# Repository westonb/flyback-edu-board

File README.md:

# flyback-edu-board
A basic flyback converter optimized for teaching educational labs. 
Designed for Stanford's EE 254 and optimized for the JLC assembly service. 

The board is based on the [UC3482B](https://www.onsemi.com/pdf/datasheet/uc3842b-d.pdf) current mode controller IC and provides a regulated 5V output than can be used to charge a phone. 

The board is designed to aid in teaching fundamentals of power electronics, lab techniques, and control theory. 
It is designed with test points on most relevant circuit nodes. 
The primary and secondary current can be measured with the shunt resistors on the PCB, so most work on the board can be done without the use of a current probe. 

In line with the educational goals the board is designed for low cost assembly. The kicad schematic includes LCSC part numbers for assembly at JLC. At 2023 prices a 25 unit build is <$15 with the JLC PCBA service. 

PCB designed in KICAD 6.

## Specifications
|   |   |
| -------- | -------- |
| Input Voltage | 12V - 36V |
| Output Voltage| 5V |
| Output Current | 1.5A |

## Features
- Built in DC and stepped resistive load
- USB A output
- Short and reverse polarity protection
- Output protected from over-voltage due to regulation fault
- Test points on critical circuit nodes
- Switchable between direct and opto-isolated voltage regulation loops

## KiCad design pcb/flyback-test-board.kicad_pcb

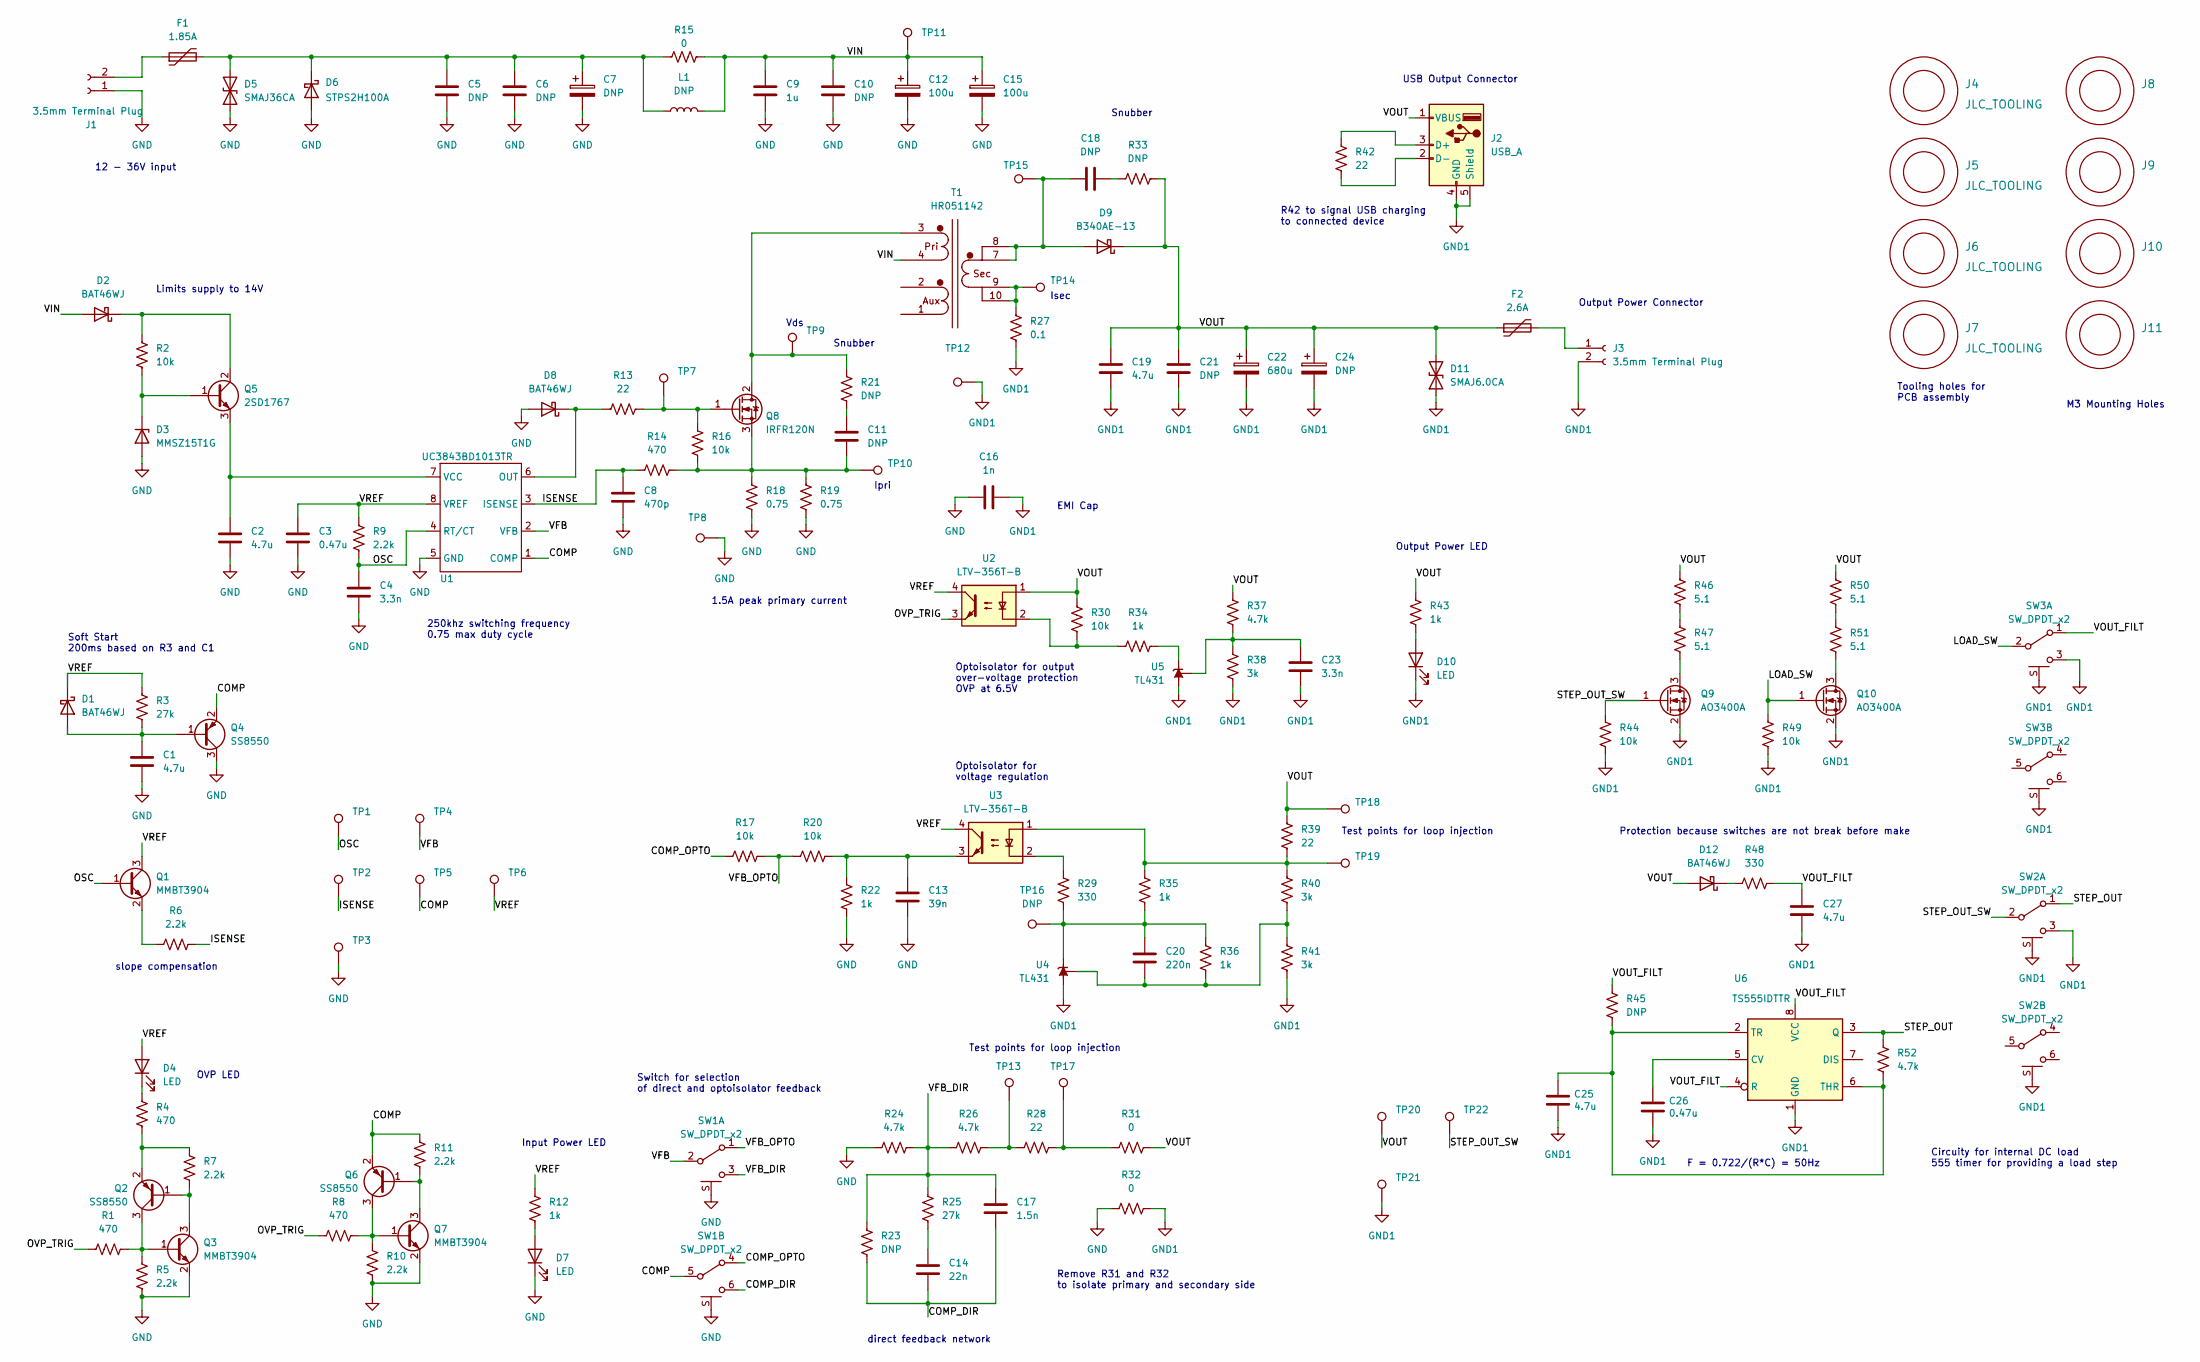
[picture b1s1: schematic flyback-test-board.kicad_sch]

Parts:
C1: 4.7u; C_0603_1608Metric_Pad1.08x0.95mm_HandSolder; MPN CL10A475KO8NNNC; JLC_MPN C19666
C2, C19, C27: 4.7u; C_0805_2012Metric_Pad1.18x1.45mm_HandSolder; MPN CL21A475KAQNNNE; JLC_MPN C1779
C3, C26: 0.47u; C_0603_1608Metric_Pad1.08x0.95mm_HandSolder; MPN CL10B474KA8NNNC; JLC_MPN C1623
C4, C23: 3.3n; C_0603_1608Metric_Pad1.08x0.95mm_HandSolder; MPN CL10B332KB8NNNC; JLC_MPN C1613
C5, C6, C10, C11, C18, C21: DNP; C_0805_2012Metric_Pad1.18x1.45mm_HandSolder
C7, C24: DNP; CP_Radial_D8.0mm_P3.50mm
C8: 470p; C_0603_1608Metric_Pad1.08x0.95mm_HandSolder; MPN 0603B471K500NT; JLC_MPN C1620
C9: 1u; C_0805_2012Metric_Pad1.18x1.45mm_HandSolder; MPN CL21B105KBFNNNE; JLC_MPN C28323
C12, C15: 100u; CP_Radial_D8.0mm_P3.50mm; MPN 50ZLH100MEFC8X11.5; JLC_MPN C109393
C13: 39n; C_0603_1608Metric_Pad1.08x0.95mm_HandSolder; MPN CC0603KRX7R9BB393; JLC_MPN C107091
C14: 22n; C_0603_1608Metric_Pad1.08x0.95mm_HandSolder; MPN CL10B223KB8NNNC; JLC_MPN C21122
C16: 1n; C_1206_3216Metric_Pad1.33x1.80mm_HandSolder; MPN 1206B102K202NT; JLC_MPN C9196
C17: 1.5n; C_0603_1608Metric_Pad1.08x0.95mm_HandSolder; MPN 0603B152K500NT; JLC_MPN C1595
C20: 220n; C_0603_1608Metric_Pad1.08x0.95mm_HandSolder; MPN GCM188R71H224KA64D; JLC_MPN C97857
C22: 680u; CP_Radial_D8.0mm_P3.50mm; MPN 16ZLH680MEFC8X16; JLC_MPN C88760
C25: 4.7u; C_0603_1608Metric_Pad1.08x0.95mm_HandSolder
D1, D2, D8, D12: BAT46WJ; D_SOD-323; MPN BAT46WJ,115; JLC_MPN C114696
D3: MMSZ15T1G; D_SOD-123; MPN MMSZ15T1G; JLC_MPN C27754
D4, D7, D10: LED; LED_0603_1608Metric; MPN 19-213/Y2C-CQ2R2L/3T(CY); JLC_MPN C72038
D5: SMAJ36CA; D_SMA; MPN SMAJ36CA/TR13; JLC_MPN C87270
D6: STPS2H100A; D_SMA; MPN STPS2H100A; JLC_MPN C81548
D9: B340AE-13; D_SMA; MPN B340AE-13; JLC_MPN C168859
D11: SMAJ6.0CA; D_SMA; MPN SMAJ6.0CA; JLC_MPN C10759
F1: 1.85A; Fuse_2920_7451Metric; MPN ASMD2920-185; JLC_MPN C135379
F2: 2.6A; Fuse_1812_4532Metric; MPN SMD1812P260TF/16; JLC_MPN C20814
J1, J3: 3.5mm Terminal Plug; Terminal-block-plug_2x1_3.5mm-pitch; MPN XY2500R-G-3.5-2P; JLC_MPN C880572
J2: USB_A; USB_A_Stewart_SS-52100-001_Horizontal; MPN 902-141A1011D10100; JLC_MPN C42643
J4, J5, J6, J7: JLC_TOOLING; JLC_TOOLING_HOLE
J8, J9, J10, J11: DNP; M3-mounting-hole-insulated
L1: DNP; L_Radial_D12.0mm_P5.00mm_Fastron_11P
Q1, Q3, Q7: MMBT3904; SOT-23; MPN MMBT3904; JLC_MPN C20526
Q2, Q4, Q6: SS8550; SOT-23; MPN SS8550; JLC_MPN C8542
Q5: 2SD1767; SOT-89-3; MPN 2SD1767T100Q; JLC_MPN C24250
Q8: IRFR120N; TO-252-2; MPN IRFR120NTRPBF; JLC_MPN C3008
Q9, Q10: AO3400A; SOT-23; MPN AO3400A; JLC_MPN C20917
R1, R4, R8, R14: 470; R_0603_1608Metric_Pad0.98x0.95mm_HandSolder; MPN 0603WAF4700T5E; JLC_MPN C23179
R2, R16, R17, R20, R30, R44, R49: 10k; R_0603_1608Metric_Pad0.98x0.95mm_HandSolder; MPN 0603WAF1002T5E; JLC_MPN C25804
R3, R25: 27k; R_0603_1608Metric_Pad0.98x0.95mm_HandSolder; MPN 0603WAF2702T5E; JLC_MPN C22967
R5, R6, R7, R9, R10, R11: 2.2k; R_0603_1608Metric_Pad0.98x0.95mm_HandSolder; MPN 0603WAF2201T5E; JLC_MPN C4190
R12, R22, R34, R35, R36, R43: 1k; R_0603_1608Metric_Pad0.98x0.95mm_HandSolder; MPN 0603WAF1001T5E; JLC_MPN C21190
R13, R28, R39, R42: 22; R_0603_1608Metric_Pad0.98x0.95mm_HandSolder; MPN 0603WAF220JT5E; JLC_MPN C23345
R15, R31, R32: 0; R_1206_3216Metric_Pad1.30x1.75mm_HandSolder; MPN 1206W4F0000T5E; JLC_MPN C17888
R18, R19: 0.75; R_1206_3216Metric_Pad1.30x1.75mm_HandSolder; MPN FRL1206FR750TS; JLC_MPN C2907360
R21, R33: DNP; R_1206_3216Metric_Pad1.30x1.75mm_HandSolder
R23, R45: DNP; R_0603_1608Metric_Pad0.98x0.95mm_HandSolder
R24, R26, R37, R52: 4.7k; R_0603_1608Metric_Pad0.98x0.95mm_HandSolder; MPN 0603WAF4701T5E; JLC_MPN C23162
R27: 0.1; R_1206_3216Metric_Pad1.30x1.75mm_HandSolder; MPN 1206W4F100LT5E; JLC_MPN C25334
R29, R48: 330; R_0603_1608Metric_Pad0.98x0.95mm_HandSolder; MPN 0603WAF3300T5E; JLC_MPN C23138
R38, R40, R41: 3k; R_0603_1608Metric_Pad0.98x0.95mm_HandSolder; MPN 0603WAF3001T5E; JLC_MPN C4211
R46, R47, R50, R51: 5.1; R_Axial_DIN0414_L11.9mm_D4.5mm_P15.24mm_Horizontal; MPN MOF2WS-5.1Ω±5% T; JLC_MPN C121605
SW1, SW2, SW3: SW_DPDT_x2; Switch_DPDT_OS202011MS2QS1; MPN SS22D03L5; JLC_MPN C609823
T1: HR051142; Transformer_POE13P; MPN HR051142; JLC_MPN C55680
TP1, TP2, TP4, TP5, TP6, TP7, TP8, TP9, TP10, TP11, TP12, TP14, TP15, TP16, TP20, TP22: DNP; THM_MINI
TP3, TP21: 5011; THM_COMPACT; MPN 5011; JLC_MPN C238127
TP13, TP17, TP18, TP19: RH-5012; THM_COMPACT; MPN RH-5012; JLC_MPN C5199815
U1: UC3843BD1013TR; SO-8_3.9x4.9mm_P1.27mm; MPN UC3843BD1013TR; JLC_MPN C92746
U2, U3: LTV-356T-B; SO-4_4.4x3.6mm_P2.54mm; MPN LTV-356T-B; JLC_MPN C10804
U4, U5: TL431; SOT-23; MPN TL431AFDT,215; JLC_MPN C97758
U6: TS555IDTTR; SOIC-8_3.9x4.9mm_P1.27mm; MPN TS555IDTTR; JLC_MPN C880084

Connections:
/COMP: Q4.2 (E), Q6.2 (E), R11.1, SW1.5 (B), TP5.1, U1.1 (COMP)
/COMP_DIR: C14.2, C17.2, R23.2, SW1.6 (C)
/COMP_OPTO: R17.2, SW1.4 (A)
/ISENSE: C8.1, R6.1, R14.2, TP2.1, U1.3 (ISENSE)
/LOAD_SW: Q10.1 (G), R49.2, SW3.2 (B)
/OSC: C4.1, Q1.1 (B), R9.2, TP1.1, U1.4 (RT/CT)
/OVP_TRIG: R1.1, R8.1, U2.3
/STEP_OUT: R52.1, SW2.1 (A), U6.3 (Q)
/STEP_OUT_SW: Q9.1 (G), R44.2, SW2.2 (B), TP22.1
/VFB: SW1.2 (B), TP4.1, U1.2 (VFB)
/VFB_DIR: C17.1, R23.1, R24.1, R25.1, R26.2, SW1.3 (C)
/VFB_OPTO: R17.1, R20.2, SW1.1 (A)
/VIN: C9.1, C10.1, C12.1, C15.1, D2.2 (A), L1.2, R15.2, T1.4 (Pri_M), TP11.1
/VOUT: C19.1, C21.1, C22.1, C24.1, D9.1 (K), D11.2 (A2), D12.2 (A), F2.1, J2.1 (VBUS), R30.2, R31.1, R33.1, R37.2, R39.1, R43.2, R46.1, R50.1, TP18.1, TP20.1, U2.1
/VOUT_FILT: C27.1, R45.1, R48.2, SW3.1 (A), U6.4 (R), U6.8 (VCC)
/VREF: C3.1, D1.1 (K), D4.2 (A), Q1.3 (C), R3.1, R9.1, R12.2, TP6.1, U1.8 (VREF), U2.4, U3.4
GND: C1.2, C2.2, C3.2, C4.2, C5.2, C6.2, C7.2, C8.2, C9.2, C10.2, C12.2, C13.2, C15.2, C16.1, D3.2 (A), D5.1 (A1), D6.2 (A), D7.1 (K), D8.2 (A), J1.1, Q3.2 (E), Q4.3 (C), Q7.2 (E), R5.2, R10.2, R18.1, R19.1, R22.1, R24.2, R32.2, SW1.S, TP3.1, TP8.1, U1.5 (GND)
GND1: C16.2, C19.2, C21.2, C22.2, C23.2, C24.2, C25.1, C26.1, C27.2, D10.1 (K), D11.1 (A1), J2.4 (GND), J2.5 (Shield), J3.2, Q9.2 (S), Q10.2 (S), R27.2, R32.1, R38.1, R41.2, R44.1, R49.1, SW2.3 (C), SW2.S, SW3.3 (C), SW3.S, TP12.1, TP21.1, U4.3 (A), U5.3 (A), U6.1 (GND)
unnamed: C1.1, D1.2 (A), Q4.1 (B), R3.2
unnamed: C2.1, Q5.3 (E), U1.7 (VCC)
unnamed: C5.1, C6.1, C7.1, D5.2 (A2), D6.1 (K), F1.2, L1.1, R15.1
unnamed: C11.1, R21.1
unnamed: C11.2, Q8.3 (S), R14.1, R16.1, R18.2, R19.2, TP10.1
unnamed: C13.1, R20.1, R22.2, U3.3
unnamed: C14.1, R25.2
unnamed: C18.1, D9.2 (A), T1.7 (SEC_P), T1.8 (SEC_P), TP15.1
unnamed: C18.2, R33.2
unnamed: C20.1, R29.2, R35.2, R36.1, TP16.1, U4.1 (K)
unnamed: C20.2, R36.2, R40.2, R41.1, U4.2 (REF)
unnamed: C23.1, R37.1, R38.2, U5.2 (REF)
unnamed: C25.2, R45.2, R52.2, U6.2 (TR), U6.6 (THR)
unnamed: C26.2, U6.5 (CV)
unnamed: D2.1 (K), Q5.2 (C), R2.1
unnamed: D3.1 (K), Q5.1 (B), R2.2
unnamed: D4.1 (K), R4.1
unnamed: D7.2 (A), R12.1
unnamed: D8.1 (K), R13.1, U1.6 (OUT)
unnamed: D10.2 (A), R43.1
unnamed: D12.1 (K), R48.1
unnamed: F1.1, J1.2
unnamed: F2.2, J3.1
unnamed: J2.2 (D-), R42.1
unnamed: J2.3 (D+), R42.2
unnamed: Q1.2 (E), R6.2
unnamed: Q2.1 (B), Q3.3 (C), R7.2
unnamed: Q2.2 (E), R4.2, R7.1
unnamed: Q2.3 (C), Q3.1 (B), R1.2, R5.1
unnamed: Q6.1 (B), Q7.3 (C), R11.2
unnamed: Q6.3 (C), Q7.1 (B), R8.2, R10.1
unnamed: Q8.1 (G), R13.2, R16.2, TP7.1
unnamed: Q8.2 (D), R21.2, T1.3 (Pri_P), TP9.1
unnamed: Q9.3 (D), R47.2
unnamed: Q10.3 (D), R51.2
unnamed: R26.1, R28.2, TP13.1
unnamed: R27.1, T1.9 (SEC_M), T1.10 (SEC_M), TP14.1
unnamed: R28.1, R31.2, TP17.1
unnamed: R29.1, U3.2
unnamed: R30.1, R34.2, U2.2
unnamed: R34.1, U5.1 (K)
unnamed: R35.1, R39.2, R40.1, TP19.1, U3.1
unnamed: R46.2, R47.1
unnamed: R50.2, R51.1

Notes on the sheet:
Limits supply to 14V
M3 Mounting Holes
Snubber
F = 0.722/(R*C) = 50Hz
250khz switching frequency 0.75 max duty cycle
slope compensation
Ipri
EMI Cap
Isec
Test points for loop injection
R42 to signal USB charging to connected device
direct feedback network
Protection because switches are not break before make
Circuity for internal DC load 555 timer for providing a load step
Output Power LED
Input Power LED
Tooling holes for PCB assembly
1.5A peak primary current
Switch for selection of direct and optoisolator feedback
Output Power Connector
Vds
Remove R31 and R32 to isolate primary and secondary side
Soft Start 200ms based on R3 and C1
OVP LED
12 - 36V input
Optoisolator for voltage regulation
Optoisolator for output over-voltage protection OVP at 6.5V
USB Output Connector

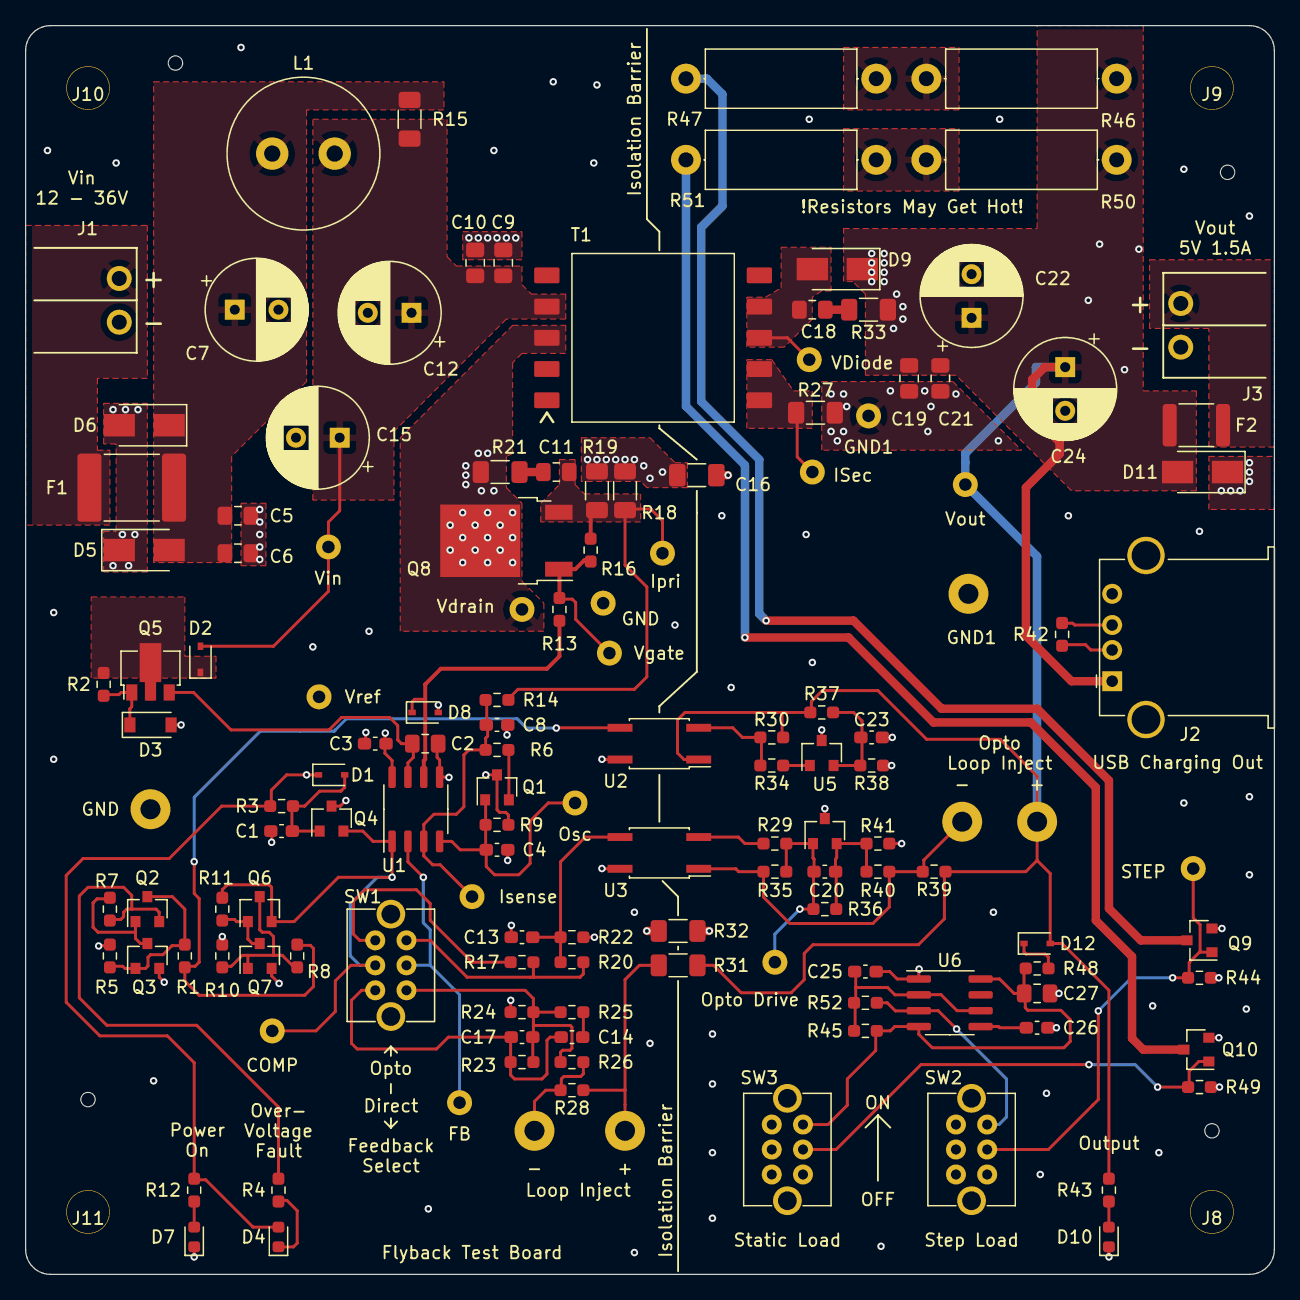
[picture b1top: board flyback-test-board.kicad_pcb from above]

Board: 4 copper layers, 100.0 x 100.0 mm, 147 parts (0 on the bottom side), 62 nets.
